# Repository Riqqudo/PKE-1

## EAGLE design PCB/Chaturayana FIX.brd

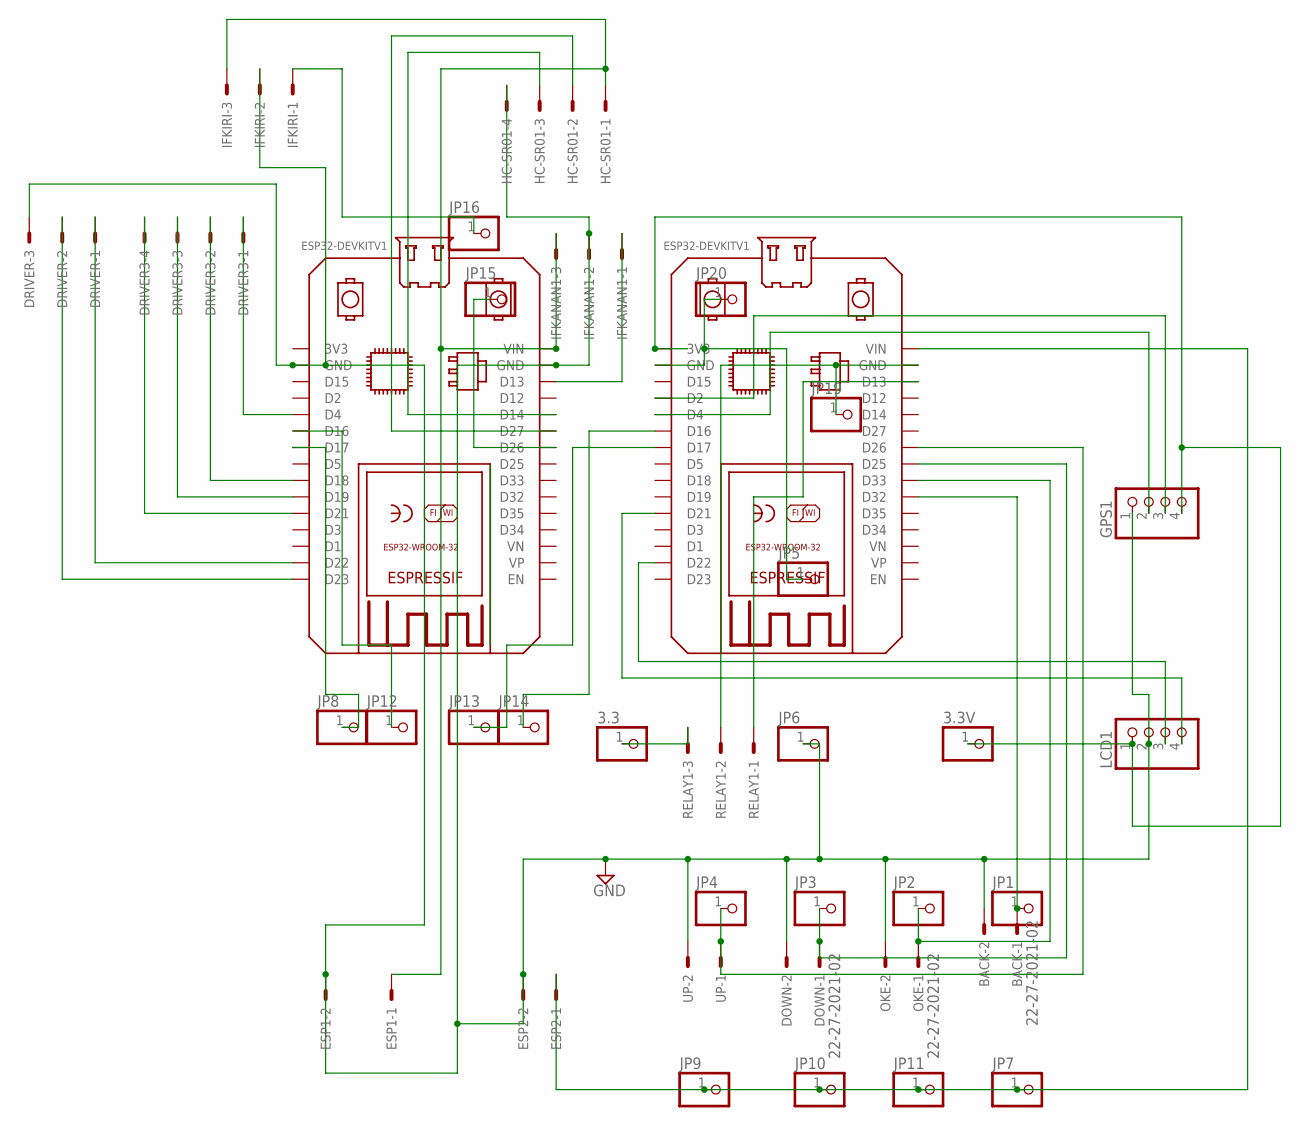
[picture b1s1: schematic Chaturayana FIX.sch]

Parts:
3.3, 3.3V: PINHD-1X1; 1X01
BACK: 22-27-2021-02; 6410-02
BOARD2, BOARD3: ESP32DEVKITV1; ESP32-DEVKITV1
DOWN: 22-27-2021-02; 6410-02
DRIVER: 22-27-2031-03; 6410-03
DRIVER3: 22-27-2041-04; 6410-04
ESP1, ESP2: 22-27-2021-02; 6410-02
GPS1: PINHD-1X4; 1X04
HC-SR01: 22-27-2041-04; 6410-04
IFKANAN1: 22-27-2031-03; 6410-03
IFKIRI: 22-27-2031-03; 6410-03
JP1, JP2, JP3, JP4, JP5, JP6, JP7, JP8, JP9, JP10, JP11, JP12, JP13, JP14, JP15, JP16, JP19, JP20: PINHD-1X1; 1X01
LCD1: PINHD-1X4; 1X04
OKE: 22-27-2021-02; 6410-02
RELAY1: 22-27-2031-03; 6410-03
UP: 22-27-2021-02; 6410-02

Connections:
2: BOARD3.D2, GPS1.3
4: BOARD2.D4, DRIVER3.1
4.: BOARD3.D4, GPS1.2
13: BOARD2.D13, IFKANAN1.1
13.: BOARD3.D13, RELAY1.1
14: BOARD2.D14, HC-SR01.3
16: BOARD3.D16, JP14.1
16..: BOARD2.D16, JP12.1
17: BOARD2.D17, JP8.1
17.: BOARD3.D17, JP13.1
18: BOARD2.D18, DRIVER3.2
19: BOARD2.D19, DRIVER3.3
21: BOARD2.D21, DRIVER3.4
21.: BOARD3.D21, LCD1.4
22: BOARD2.D22, DRIVER.1
22.: BOARD3.D22, LCD1.3
23: BOARD2.D23, DRIVER.2
25: BOARD3.D25, DOWN.1, JP3.1
26.: BOARD2.D26, JP15.1
26..: BOARD3.D26, JP4.1, UP.1
27: BOARD2.D27, HC-SR01.2
32: BACK.1, BOARD3.D32, JP1.1
33: BOARD3.D33, JP2.1, OKE.1
GND: BACK.2, BOARD2.GND, BOARD2.GND@1 (GND), DOWN.2, DRIVER.3, ESP1.2, ESP2.2, GPS1.1, HC-SR01.4, IFKANAN1.2, IFKIRI.2, JP6.1, LCD1.2, OKE.2, UP.2
unnamed: IFKIRI.1, JP16.1
unnamed: BOARD3.GND, JP19.1, RELAY1.2
unnamed: 3.3.1, RELAY1.3
unnamed: 3.3V.1, BOARD3.3V3, GPS1.4, LCD1.1
unnamed: BOARD3.GND@1 (GND), JP5.1, JP20.1
unnamed: BOARD2.VIN, ESP1.1, HC-SR01.1, IFKANAN1.3, IFKIRI.3
VCC: BOARD3.VIN, ESP2.1, JP7.1, JP9.1, JP10.1, JP11.1

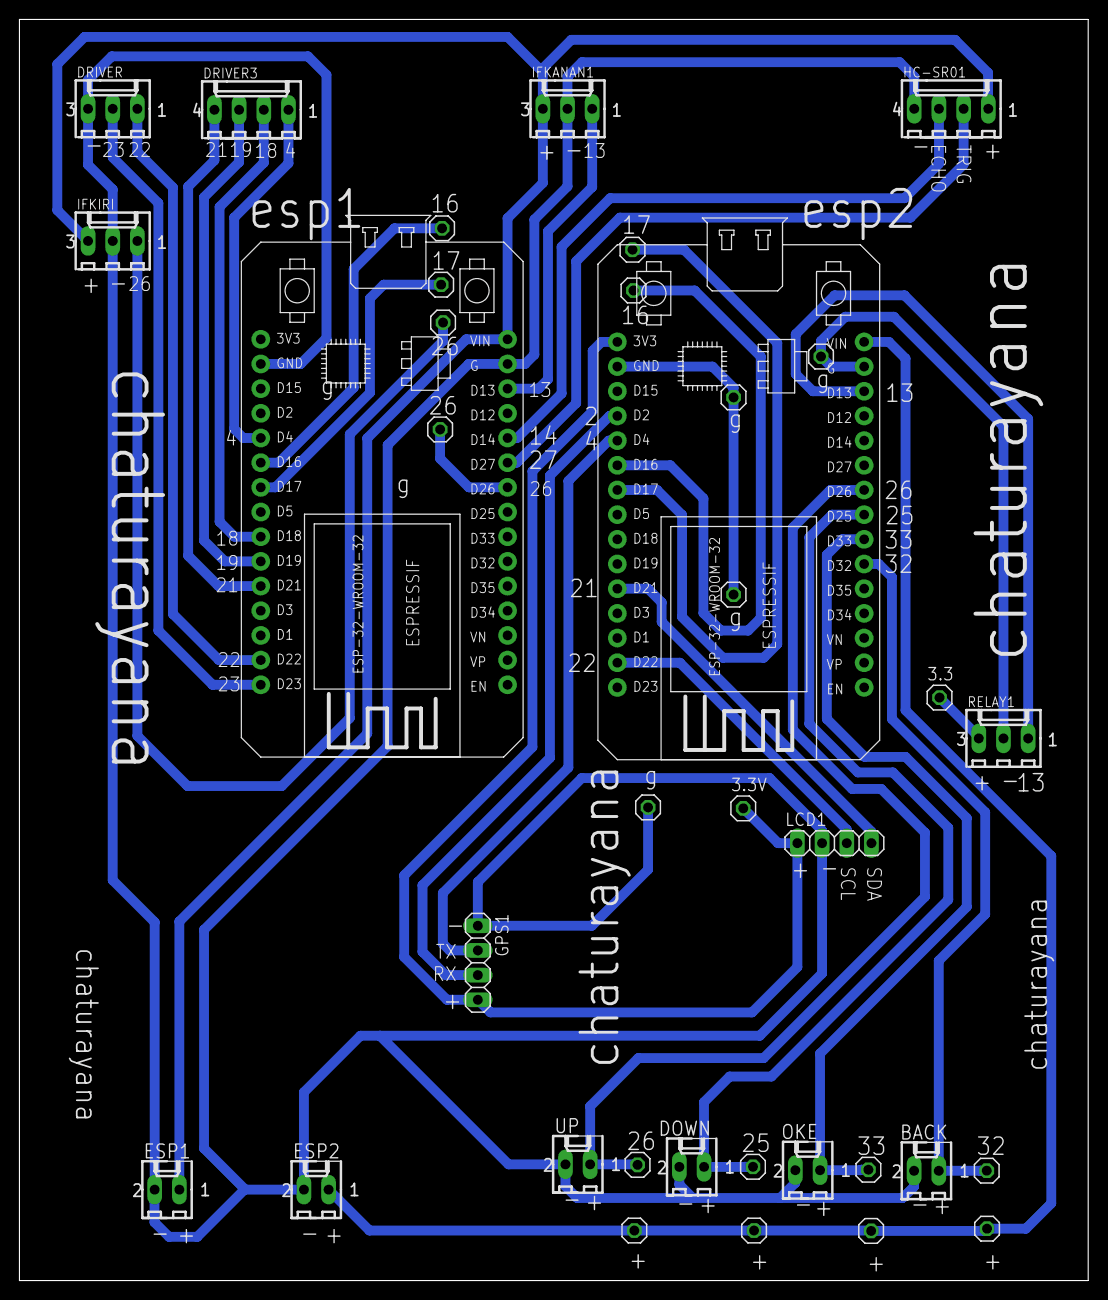
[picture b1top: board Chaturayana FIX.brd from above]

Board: 2 copper layers, 110.0 x 129.8 mm, 36 parts (0 on the bottom side), 31 nets.

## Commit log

2024-12-02 Create Codingan
2024-12-02 Create ok
2024-12-02 Update ok
2024-12-02 Delete/ ok
2024-12-02 Create temp
2024-12-02 Create li
2024-12-02 Rename Full Body & Komponen.rar to Chaturayana Full.rar
2024-12-02 Update temp
2024-12-02 Rename temp to temp.gitignore
2024-12-02 Rename temp.gitignore to temp
2024-12-02 Create o
2024-12-02 Create l
